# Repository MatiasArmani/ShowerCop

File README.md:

# ShowerCop: Un Dispositivo Inteligente para un Baño Eficiente y Responsable

## Descripción del Proyecto

**ShowerCop** es un dispositivo innovador diseñado para fomentar un uso más responsable del agua durante el momento del baño. Creado para ser colocado cerca de la ducha, **ShowerCop** monitorea en tiempo real la duración de cada ducha y el consumo estimado de agua, proporcionando alertas y mensajes en diferentes etapas del baño para guiar al usuario a través de un proceso más eficiente y consciente.

## Características Principales

1. **Monitoreo del Tiempo y Consumo de Agua**
   - ShowerCop comienza a calcular el tiempo de ducha desde el momento en que se activa y, utilizando una configuración basada en estimaciones de caudal estándar, determina la cantidad de agua que se está utilizando.
  
2. **Reproducción de Música**
   - Para hacer la experiencia más amena y divertida, el dispositivo reproduce música mientras se monitorea el tiempo de ducha. Se pueden preconfigurar listas de reproducción o seleccionar canciones según la duración prevista del baño.
  
3. **Avisos de Etapas**
   - Durante el baño, ShowerCop proporciona alertas basadas en etapas preestablecidas (por ejemplo, mojado inicial, enjabonado, aclarado, etc.), guiando al usuario para completar cada etapa en un tiempo recomendado y evitar el derroche de agua.
  
4. **Mensajes de Concientización**
   - Al finalizar el baño, el dispositivo solicita al usuario que indique si ha terminado. En función del tiempo total, ShowerCop proporciona un mensaje personalizado:
     - **Si se excede el tiempo recomendado:** Un mensaje educativo y de concientización indica la cantidad de agua derrochada y sugiere alternativas de uso más consciente. Por ejemplo, puede mencionar cuánto tiempo de agua potable equivalente se desperdició o cómo podría haberse utilizado para otras necesidades.
     - **Si se respeta el tiempo óptimo:** ShowerCop felicita al usuario por su eficiencia y resalta el impacto positivo de su acción en la conservación del agua.
  
5. **Objetivo**
   - ShowerCop está diseñado para ayudar a reducir el tiempo promedio de baño, incentivando a los usuarios a ser más conscientes de su consumo de agua, sin sacrificar la experiencia de una ducha relajante.

## Beneficios de Uso

- **Conciencia ambiental:** Promueve hábitos sostenibles de uso de agua, contribuyendo a la reducción del consumo doméstico.
- **Interactividad:** Transforma una actividad cotidiana en un reto personal, haciendo del baño una experiencia educativa.
- **Impacto social:** A través de la educación en el uso responsable del agua, ShowerCop busca influir en comunidades y hogares, resaltando la importancia de pequeños cambios en los hábitos diarios para un impacto significativo.

## Tecnologías Utilizadas

- **Sensor de flujo** para la estimación de consumo de agua.
- **Altavoz incorporado** para reproducción de música.
- **Pantalla LED** para visualizar alertas y etapas del baño.
- **Microcontrolador** para gestión de tiempos y lógica de control.
  
## Casos de Uso

**ShowerCop** es ideal para hogares, instituciones educativas y cualquier entorno donde se busque fomentar la educación en el uso responsable del agua. Además, se puede utilizar como un elemento lúdico para enseñar a los más pequeños la importancia del consumo eficiente del recurso más vital del planeta.

## Desafíos Técnicos

Durante el desarrollo, se implementaron algoritmos para ajustar los tiempos de las alertas según la duración del baño y se mejoró la precisión de las estimaciones de consumo de agua. También se diseñó una interfaz intuitiva para que el usuario pueda interactuar fácilmente con el dispositivo.

## Conclusión

**ShowerCop** representa un paso hacia la integración de la tecnología en el hogar para un futuro más sostenible y consciente, mostrando cómo el cambio comienza desde las pequeñas acciones diarias.

---

_¡Gracias por interesarte en ShowerCop! Si te gustó el proyecto, no dudes en darle un ⭐ y contribuir a su desarrollo._

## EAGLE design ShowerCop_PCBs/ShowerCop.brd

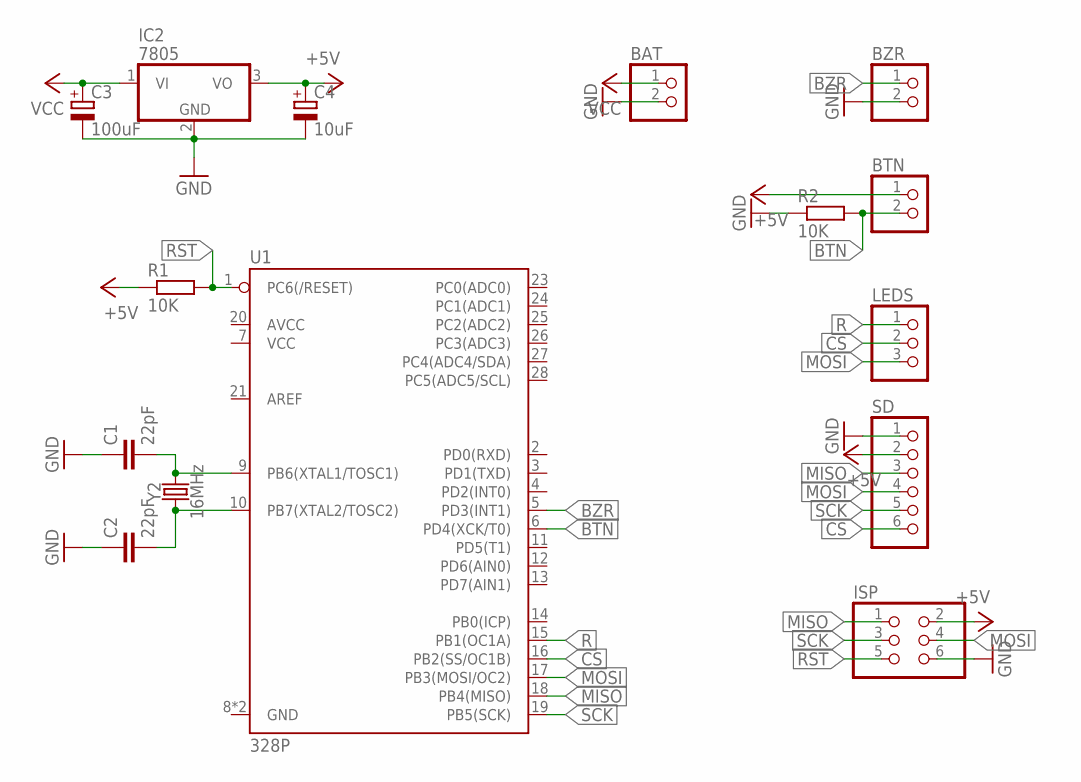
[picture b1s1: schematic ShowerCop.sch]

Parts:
BAT: PINHD-1X2; 1X02
BTN: PINHD-1X2; 1X02
BZR: PINHD-1X2; 1X02
C1, C2: 22pF; CAP-PTH-2.54
C3: 100uF; E2,5-6E
C4: 10uF; E2,5-6E
IC2: 7805; TO220V
ISP: PINHD-2X3; 2X03
LEDS: PINHD-1X3; 1X03
R1, R2: 10K; 0204/7
SD: PINHD-1X6; 1X06
U1: 328P; DIP28
Y2: 16MHz; HC49US

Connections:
+5V: BTN.1, C4.+, IC2.3 (VO), ISP.2, R1.1, SD.2
BTN: BTN.2, R2.2, U1.6 (PD4(XCK/T0))
BZR: BZR.1, U1.5 (PD3(INT1))
CS: LEDS.2, SD.6, U1.16 (PB2(SS/OC1B))
GND: BAT.2, BZR.2, C1.1, C2.1, C3.-, C4.-, IC2.2 (GND), ISP.6, R2.1, SD.1
MISO: ISP.1, SD.3, U1.18 (PB4(MISO))
MOSI: ISP.4, LEDS.3, SD.4, U1.17 (PB3(MOSI/OC2))
unnamed: C2.2, U1.10 (PB7(XTAL2/TOSC2)), Y2.1
unnamed: C1.2, U1.9 (PB6(XTAL1/TOSC1)), Y2.2
R: LEDS.1, U1.15 (PB1(OC1A))
RST: ISP.5, R1.2, U1.1 (PC6(/RESET))
SCK: ISP.3, SD.5, U1.19 (PB5(SCK))
VCC: BAT.1, C3.+, IC2.1 (VI)

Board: 2 copper layers, 15 parts (0 on the bottom side), 13 nets, no tracks yet.

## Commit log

2024-09-30 init

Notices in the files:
parts and their libraries:
SparkFun-Clocks: Licensing: Creative Commons ShareAlike 4.0 International - https://creativecommons.org/licenses/by-sa/4.0
